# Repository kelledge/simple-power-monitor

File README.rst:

Error Calculations
------------------

Voltage Divider:
100KOhm +/- 0.1%, 75PPM/C (-40C -> 80C)
100KOhm +/-
Max: 100100.08008
min 99899.92008

Voltage Reference:

Min @ 20C: 2.495
Max @ 20C: 2.505

Temp Coef: 75PPM/C

Max Temp Err @ -40C: -11.228mV
Max Temp Err @ 80C: +11.272mV

Min @ -40C: 2.4837725 => -16.227mV error
Max @ +80C: 2.5162725 => +16.272mV error

Temperature Calculations
------------------------
The only part that dissipates enough energy to matter is the current sense
resistor.

Max Power Consumption
---------------------

*Current Sense:*

Resistor:
R_sense = 7mOhm
A_max = 6A
P_max = 252mW

Amp:
V_max = 72V
A_max = 190uA
P_max = 14mW

*Voltage Reference:*

Ref In:
REF_Z_in = 250kOhm
REF_V_in = 2.5V
REF_A_in = 10uA
REF_P    = 25uW

Resistor:
R_bias = 82kOhm
V_max = (30V - 2.5V)
P_max = V_max^2/R_bias => 9.2mW

Reference:

Total:

*Voltage Divider:*
1/6 Voltage Divider Network

Calculations:
R_eq = 120K
V_max = 30V
P_max = V_max^2/R_eq => 7.5mW

Parts List
----------

+----------+------------+---------------------------+---------------------+
| Quantity | Designator | Description               | Mouser SKU          |
+----------+------------+---------------------------+---------------------+
| 1        | U1         | Current sense amplifier   | 700-MAX4081SASA     |
| 1        | R1         | Current sense resistor    | 71-WSL20107L000FEA  |
| 1        | R2         | 1/6 voltage Divider       | 71-TNPW0805100KBEEA |
| 1        | R3         | 1/6 voltage Divider       | 71-TNPW080520K0BEEA |
| 1        | U2         | Voltage reference         | 584-ADR5041WBRTZ-R7 |
| 1        | R4         | Voltage reference bias    | 71-TNPW080582K0BEEA |
| 2        | J1/J2      | 2 pin terminal receptacle | 710-691311500102    |
| 2        | -          | 2 pin terminal plug       | 710-691351500002    |
| 1        | J3         | 3 pin terminal receptacle | 651-1926028         |
| 1        | -          | 3 pin terminal plug       | 651-1911978         |
+----------+------------+---------------------------+---------------------+

RAW
---
30V Max
12V/24V

+/- 6A
5/12/24 V Input

<= 1mA Power

V

5V -> 5A
0V -> -5A

Mount
-----
http://www.mouser.com/Search/ProductDetail.aspx?R=1201578virtualkey65100000virtualkey651-1201578

Current Sense
-------------

Calculations:

Resistor:
R_sense = 7mOhm
A_max = 6A
P_max = 252mW

Amp:
V_max = 72V
A_max = 190uA
P_max = 14mW

Ref:
REF_Z_in = 250kOhm
REF_V_in = 2.5V
REF_A_in = 10uA
REF_P    = 25uW

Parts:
7mOhm: http://www.mouser.com/ProductDetail/Vishay-Dale/WSL20107L000FEA/?qs=sGAEpiMZZMtlleCFQhR%2fzb7jD%252buUxQm7%252biyfvAJP1Wo%3d
Amp: http://www.mouser.com/ProductDetail/Maxim-Integrated/MAX4081SASA+/?qs=sGAEpiMZZMutXGli8Ay4kB5dsh5iKl6TTQwfiqPU9w4%3d

Resistor: 500mW

-6A -> 0V
 0A -> 2.5V
+6A -> 5V

1mV out -> 2.4mA

Voltage Reference
-----------------
Bias: 82kOhm

Needs 60uA + 10uA: 70uA

(30-2.5)/80e3 -> 335uA
(12-2.5)/80e3 -> 115uA

REF_P_max = 9.2mW

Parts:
Ref: http://www.mouser.com/ProductDetail/Analog-Devices/ADR5041WBRTZ-R7/?qs=sGAEpiMZZMuBck1X%252b7j9fJ909qbP0fXHMqaADQNAzbA%3d
Bias: http://www.mouser.com/ProductDetail/Vishay/TNPW080582K0BEEA/?qs=222842oYAD9vR9R%252b93yFkQ%3d%3d

Divider
-------
1/6 Voltage Divider Network

Calculations:
R_eq = 120K
I_max = 250uA
P_max = 30mW

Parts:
100K: http://www.mouser.com/ProductDetail/Vishay/TNPW0805100KBEEA/?qs=sGAEpiMZZMtlubZbdhIBIFsxO9oIeGFUmiF5Rz3MCQ8%3d
20K: http://www.mouser.com/ProductDetail/Vishay/TNPW080520K0BEEA/?qs=sGAEpiMZZMtlubZbdhIBINl7pLegQti%252bok6yVk5rPfc%3d

25 PPM / C
0.1 %
125 mW (1/8 W)
150 V

Connectors
----------
3 Pin
Receptacle: http://www.mouser.com/ProductDetail/Phoenix-Contact/1926028/?qs=sGAEpiMZZMvPvGwLNS671zZvyVWS49C%252bmTXXxhDGUDA%3d
Plug: http://www.mouser.com/ProductDetail/Phoenix-Contact/1911978/?qs=sGAEpiMZZMvPvGwLNS6718PaoTt7FM7cq6nTDRCep18%3d

2 Pin
Receptacle: http://www.mouser.com/ProductDetail/Wurth-Electronics/691311500102/?qs=sGAEpiMZZMvPvGwLNS6715pX%252bQgp6lhzG3N%2f9nisyspwto99zh4GxQ%3d%3d
Plug: http://www.mouser.com/Search/ProductDetail.aspx?qs=7gQLVZk5cPkg%2frpRGyiXgA%3d%3d

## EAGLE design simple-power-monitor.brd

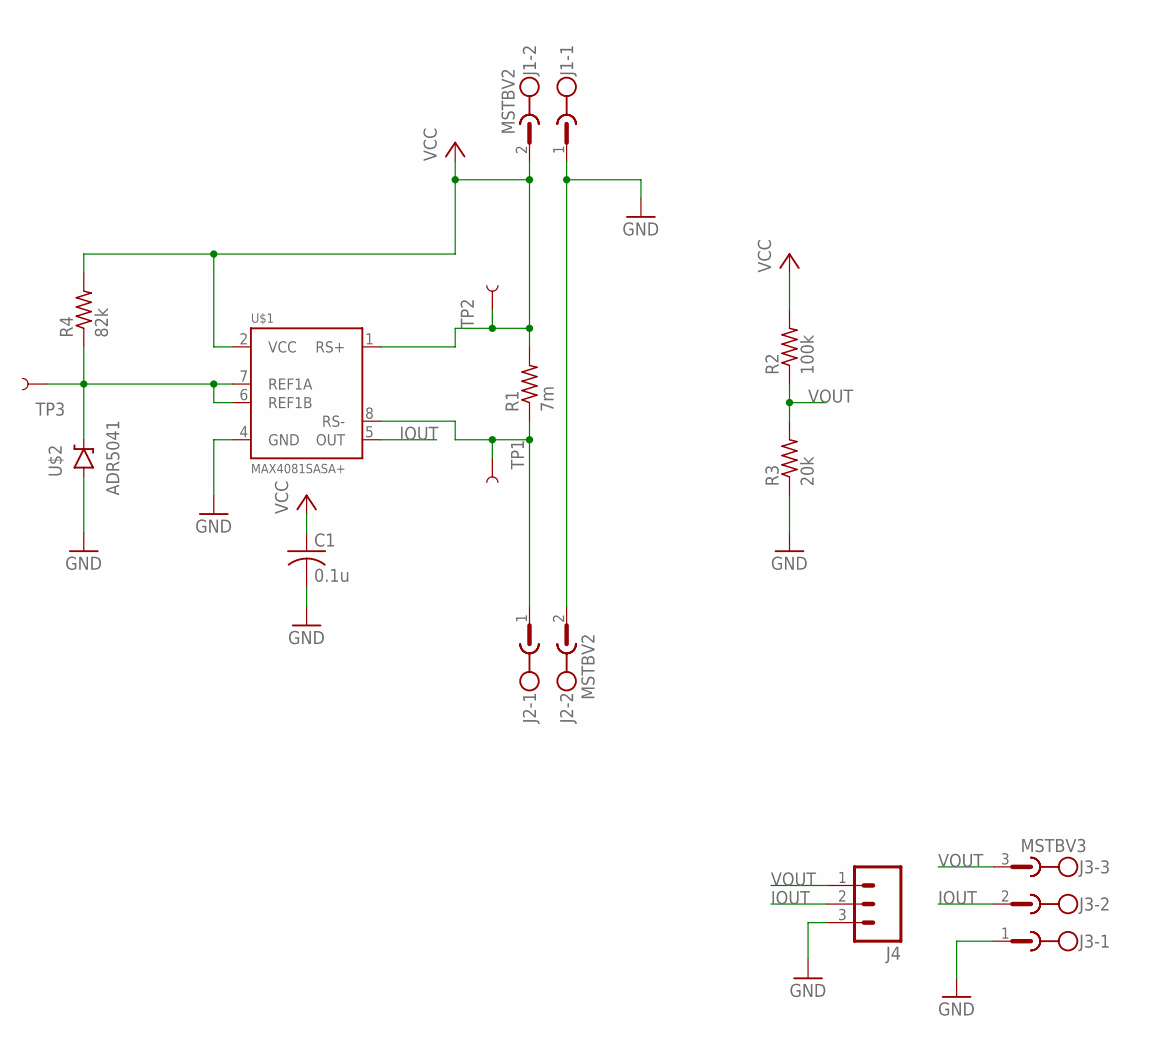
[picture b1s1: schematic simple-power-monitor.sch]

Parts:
C1: 0.1u; C0805K
J1, J2: MSTBV2
J3: MSTBV3
J4: M03PTH; 1X03
R1: 7m; R2010
R2: 100k; R0805
R3: 20k; R0805
R4: 82k; R0805
TP1, TP2, TP3: TEST-POINTTP_15TH_THRU; TP_15TH
U$1: MAX4081SASA+; SO8
U$2: ADR5041; SOT23-3

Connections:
GND: C1.2, J1.1, J2.2, J3.1, J4.3, R3.1, U$1.4 (GND), U$2.2 (A)
IOUT: J3.2, J4.2, U$1.5 (OUT)
unnamed: R4.1, TP3.P$1, U$1.6 (REF1B), U$1.7 (REF1A), U$2.1 (C)
RS+: J2.1, R1.1, TP1.P$1, U$1.8 (RS-)
VCC: C1.1, J1.2, R1.2, R2.2, R4.2, TP2.P$1, U$1.1 (RS+), U$1.2 (VCC)
VOUT: J3.3, J4.1, R2.1, R3.2

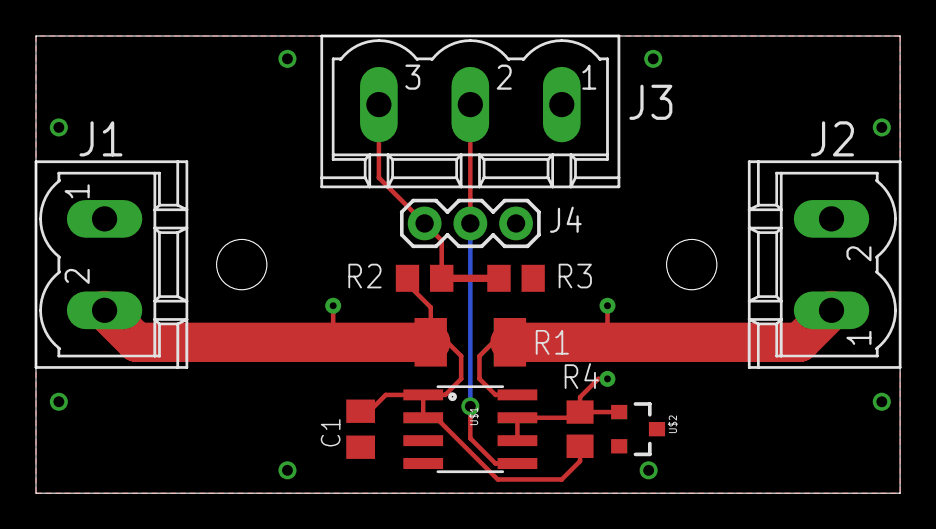
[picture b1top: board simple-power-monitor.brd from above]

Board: 2 copper layers, 48.0 x 25.4 mm, 14 parts (0 on the bottom side), 6 nets.

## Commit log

2016-09-18 readme added, sense traces updated

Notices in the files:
parts and their libraries:
SparkFun-Passives: Licensing: Creative Commons ShareAlike 4.0 International - https://creativecommons.org/licenses/by-sa/4.0
